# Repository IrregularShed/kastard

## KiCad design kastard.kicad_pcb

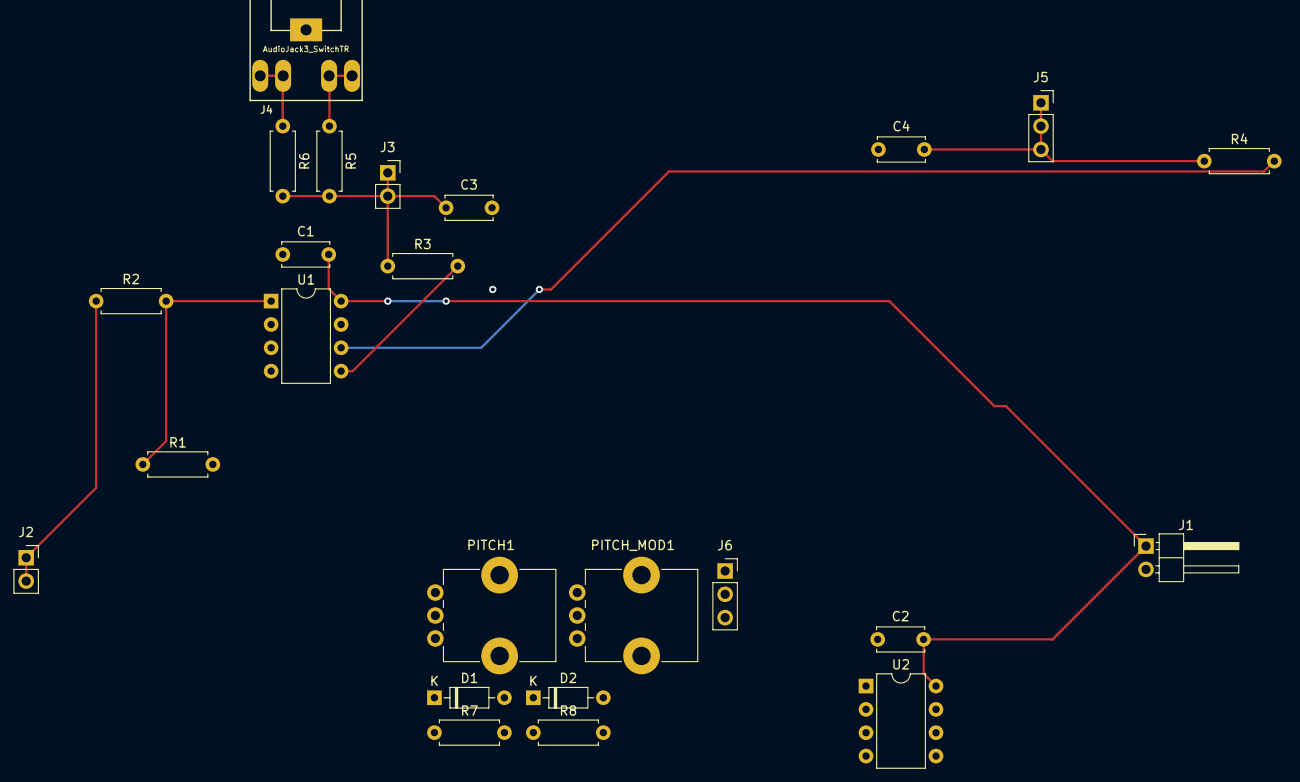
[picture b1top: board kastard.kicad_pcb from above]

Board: 2 copper layers, 24 parts (0 on the bottom side), 14 nets.

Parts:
C1, C2, C3, C4: 470nF; C_Disc_D5.0mm_W2.5mm_P5.00mm
D1, D2: Zener 5V1; D_DO-35_SOD27_P7.62mm_Horizontal
J1: Power; PinHeader_1x02_P2.54mm_Horizontal
J2: TYPE; PinSocket_1x02_P2.54mm_Vertical
J3: WAVE; PinSocket_1x02_P2.54mm_Vertical
J4: AudioJack3_SwitchTR; Tayda_3.5mm_stereo_TRS_jack_A-853
J5: P_SQR; PinSocket_1x03_P2.54mm_Vertical
J6: P_PITCH; PinSocket_1x03_P2.54mm_Vertical
PITCH1: B100K; Potentiometer_Alps_RK09K_Single_Vertical
PITCH_MOD1: B100K; Potentiometer_Alps_RK09K_Single_Vertical
R1, R7: 100K; R_Axial_DIN0207_L6.3mm_D2.5mm_P7.62mm_Horizontal
R2: 220K; R_Axial_DIN0207_L6.3mm_D2.5mm_P7.62mm_Horizontal
R3, R4, R5, R6: 1K; R_Axial_DIN0207_L6.3mm_D2.5mm_P7.62mm_Horizontal
R8: 1M; R_Axial_DIN0207_L6.3mm_D2.5mm_P7.62mm_Horizontal
U1: ATtiny85-VCO; DIP-8_W7.62mm
U2: ATtiny85-LFO; DIP-8_W7.62mm

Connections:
GND: C1.1, C2.1, C3.2, C4.1, J1.2, J4.S, PITCH1.3, PITCH_MOD1.3, R1.2, R8.2, U1.4, U2.4
unnamed: C3.1, J3.1, J3.2, R3.1, R5.2, R6.2
unnamed: C4.2, J5.1, J5.2, J5.3, R4.1
unnamed: D1.2, PITCH1.2, R7.1
unnamed: D2.2, PITCH_MOD1.2, R7.2
unnamed: J2.1, J2.2, R2.1
unnamed: J4.R, J4.RN, R5.1
unnamed: J4.T, J4.TN, R6.1
unnamed: J6.1, J6.2, J6.3, PITCH_MOD1.1
unnamed: R1.1, R2.2, U1.1
unnamed: R3.2, U1.5
unnamed: R4.2, U1.6
Pitch_Mix: D1.1, D2.1, R8.1, U1.3
VCC: C1.2, C2.2, J1.1, PITCH1.1, U1.8, U2.8

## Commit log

2021-02-04 initial commit-me-do
2021-02-04 Add a PNG of the schematic as it stands
